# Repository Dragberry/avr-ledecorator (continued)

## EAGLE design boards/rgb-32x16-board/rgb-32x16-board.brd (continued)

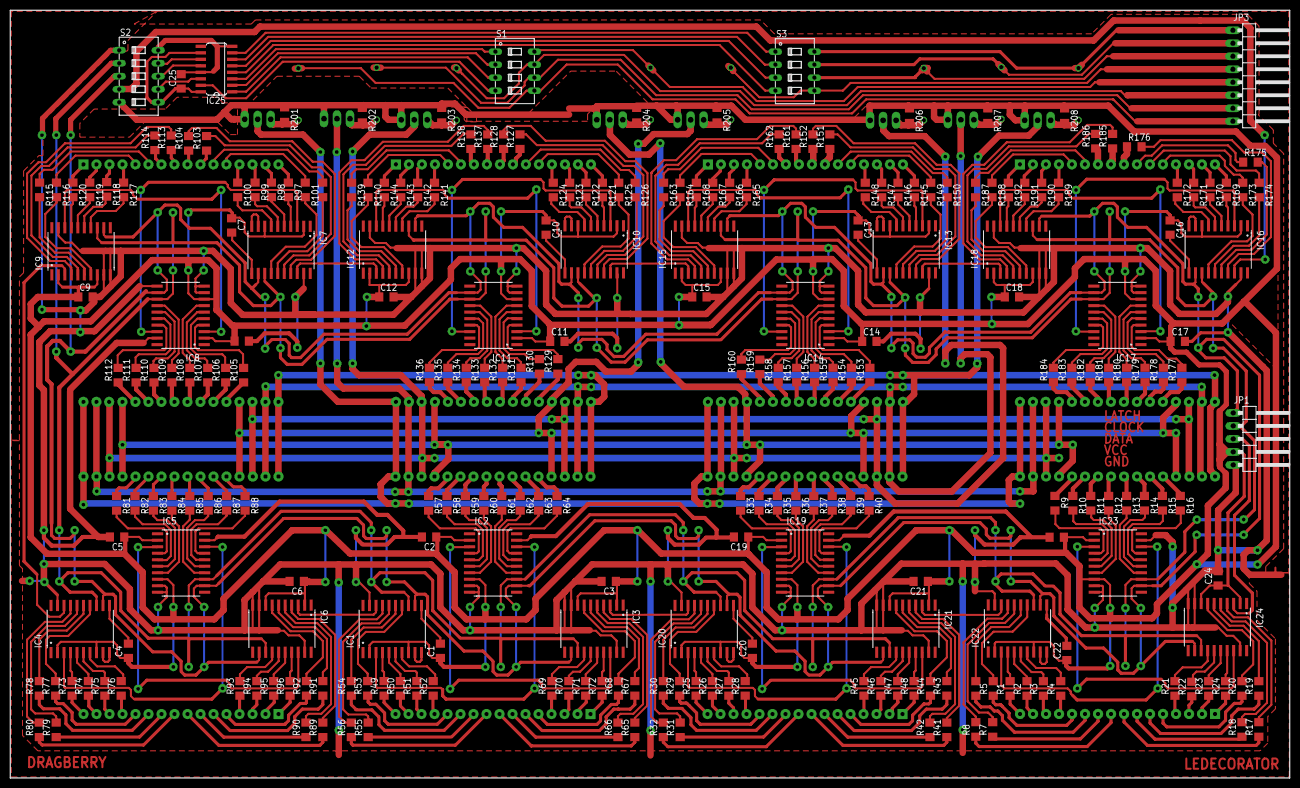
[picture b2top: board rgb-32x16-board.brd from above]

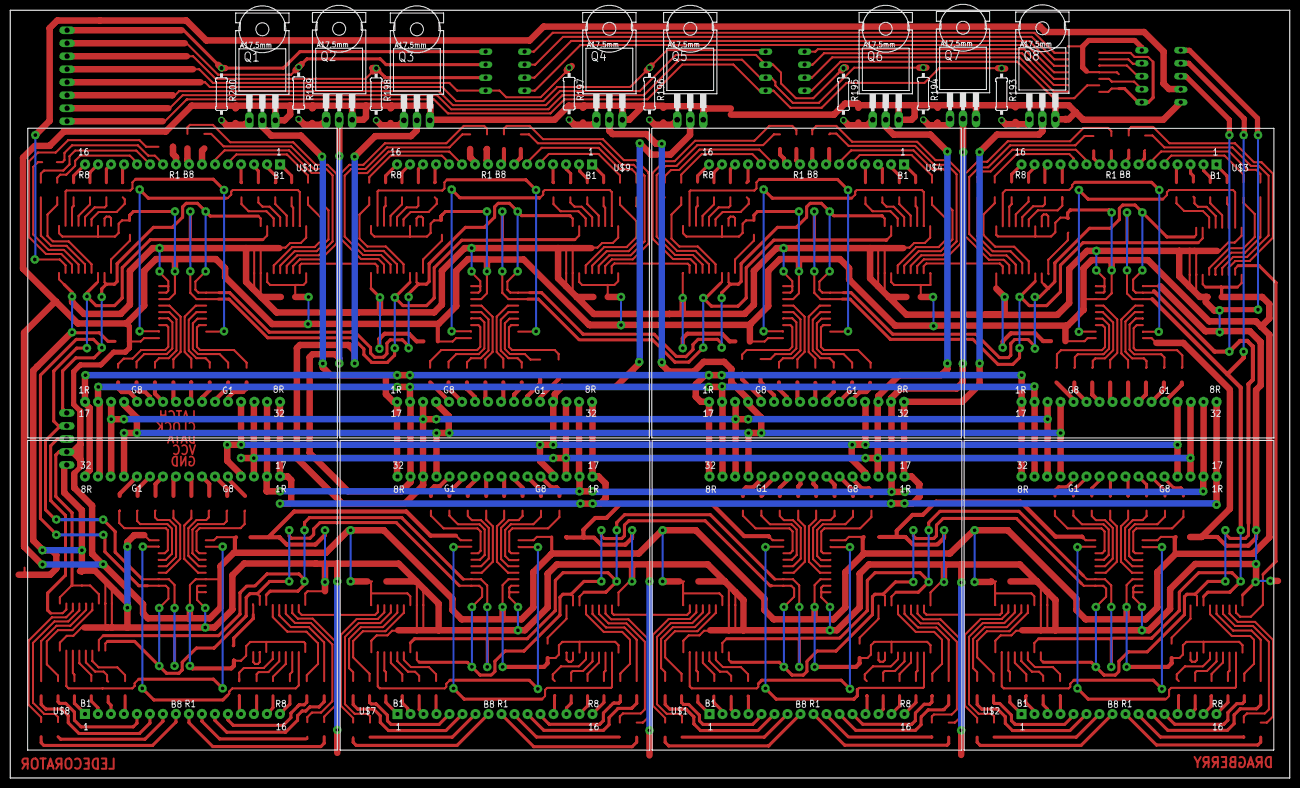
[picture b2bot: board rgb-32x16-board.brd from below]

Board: 2 copper layers, 250.0 x 150.0 mm, 279 parts (24 on the bottom side), 437 nets.

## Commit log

2019-08-13 Init commit
2019-08-14 Initial code for screen
2019-10-25 Driver init commit
2019-10-26 Snake game
2019-10-26 Fixed app stopping
2019-10-27 Life game
2019-10-29 Screen processors
2019-10-30 Screen implmentation
2019-10-30 Refactoring screen processors
2019-10-31 Uart processor
2019-11-01 Changing row selection by SPI
2019-11-01 Refactoring
2019-11-02 Remove mono screen obsolete code
2019-11-02 display schema and board
2019-11-02 Eagle libraries
2019-11-02 Byte terminal worker
2019-11-02 Workers implentation
2019-11-03 Default worker
2019-11-03 Ledecorator core init commit
2019-11-03 core
2019-11-04 Refactoring workers
2019-11-04 Workers refactoring
2019-11-04 Data transmitting with confirmation on maximum speed
2019-11-06 Core transmitting POC
2019-11-07 game life: c/10 ship
2019-11-07 Implementing core
2019-11-08 core implementation
2019-11-09 Core: screen interface implementation
2019-11-09 Snake game is moved to core
2019-11-10 Counter
2019-11-11 Draw integer numbers
2019-11-12 Printing float numbers
2019-11-12 print signed numbers
2019-11-13 Draw area
2019-11-13 Draw image (temperature icon)
2019-11-14 draw hystogram
2019-11-14 anonymous function for offsetting images
2019-11-14 offset images
2019-11-15 draw strings
2019-11-15 Running string
2019-11-18 draw number as string
2019-11-19 sensors app
2019-11-20 Sensors apps
2019-11-22 Using PROGMEM for constant images
2019-11-22 Data in progmemory
2019-11-23 Store data in prog mem
2019-11-23 String aligning
2019-11-23 I2C initial commit
2019-11-25 i2c interface
2019-11-26 Update imagemono8x8.h
    Chracters
2019-11-26 Update imagemono8x8.h
    ASCII characters
2019-11-26 draw long string
2019-11-27 Drawable string
2019-12-03 Global refactoring
2019-12-06 uart
2019-12-12 Refactoring driver
2019-12-12 3 buffers
2019-12-14 Refactoring completed
2019-12-19 Program runners
2019-12-21 refactoring display
2019-12-21 lifegame
2019-12-23 several programms
2019-12-23 multi apps
2019-12-25 Coding
2019-12-25 fix transmit protocol
2019-12-26 switching apps
2019-12-26 FPS debug
2019-12-28 life game, transmitting
2019-12-28 life game: living things
2020-01-06 bme280 stuff
2020-01-06 weather app
2020-01-06 fixes
2020-01-07 sensors hystogram
2020-01-08 Weather app - savinig values
2020-01-11 Sensors charts
2020-01-11 Sensors completed
2020-01-11 fix image
2020-01-14 clock
2020-01-17 fonts refactoring
2020-01-17 chars 5x7
2020-01-17 chars as bitmap
2020-01-17 fonts
2020-01-17 clock app
2020-01-18 clock app and calendar
2020-01-20 weather and clock
2020-01-20 Weather app - charts UX
2020-01-22 snake
2020-01-28 snake tail eating fix
2020-02-10 bluetotth transmitting
2020-02-12 BLE exchange
2020-02-13 Android app skeleton
2020-02-15 Android app implementation
2020-02-17 Android ble implementation
2020-03-29 Android impl
2020-04-11 Android BLE App
2020-04-12 Android BLE - Snake control
2020-04-12 Anroid BLE: Snake control
2020-04-12 Android BLE: Snake and orchestration
2020-04-12 Android BLE: Clock app
2020-04-13 Android BLE: Weather app
2020-04-14 Android Refactoring
2020-04-15 Android BLE: Life Game
2020-04-17 Android BLE: Orchestration
2020-04-17 Android BLE: Weather App (Humidity)
2020-04-17 Core: Percent character
2020-04-17 Core: fix timer registering
2020-04-25 Boards
2020-04-29 CORE: board
2020-05-10 Core: fix board
2020-12-01 Storing state
2020-12-03 Color selection
2020-12-04 Sandbox loading page
2020-12-06 Sandbox loading picture
2020-12-06 Sandbox loading pictures
2020-12-07 life game storing state
2020-12-10 Save and loads apps
2020-12-12 Snake settings
2020-12-13 Clock settings
2020-12-14 clock app fix
